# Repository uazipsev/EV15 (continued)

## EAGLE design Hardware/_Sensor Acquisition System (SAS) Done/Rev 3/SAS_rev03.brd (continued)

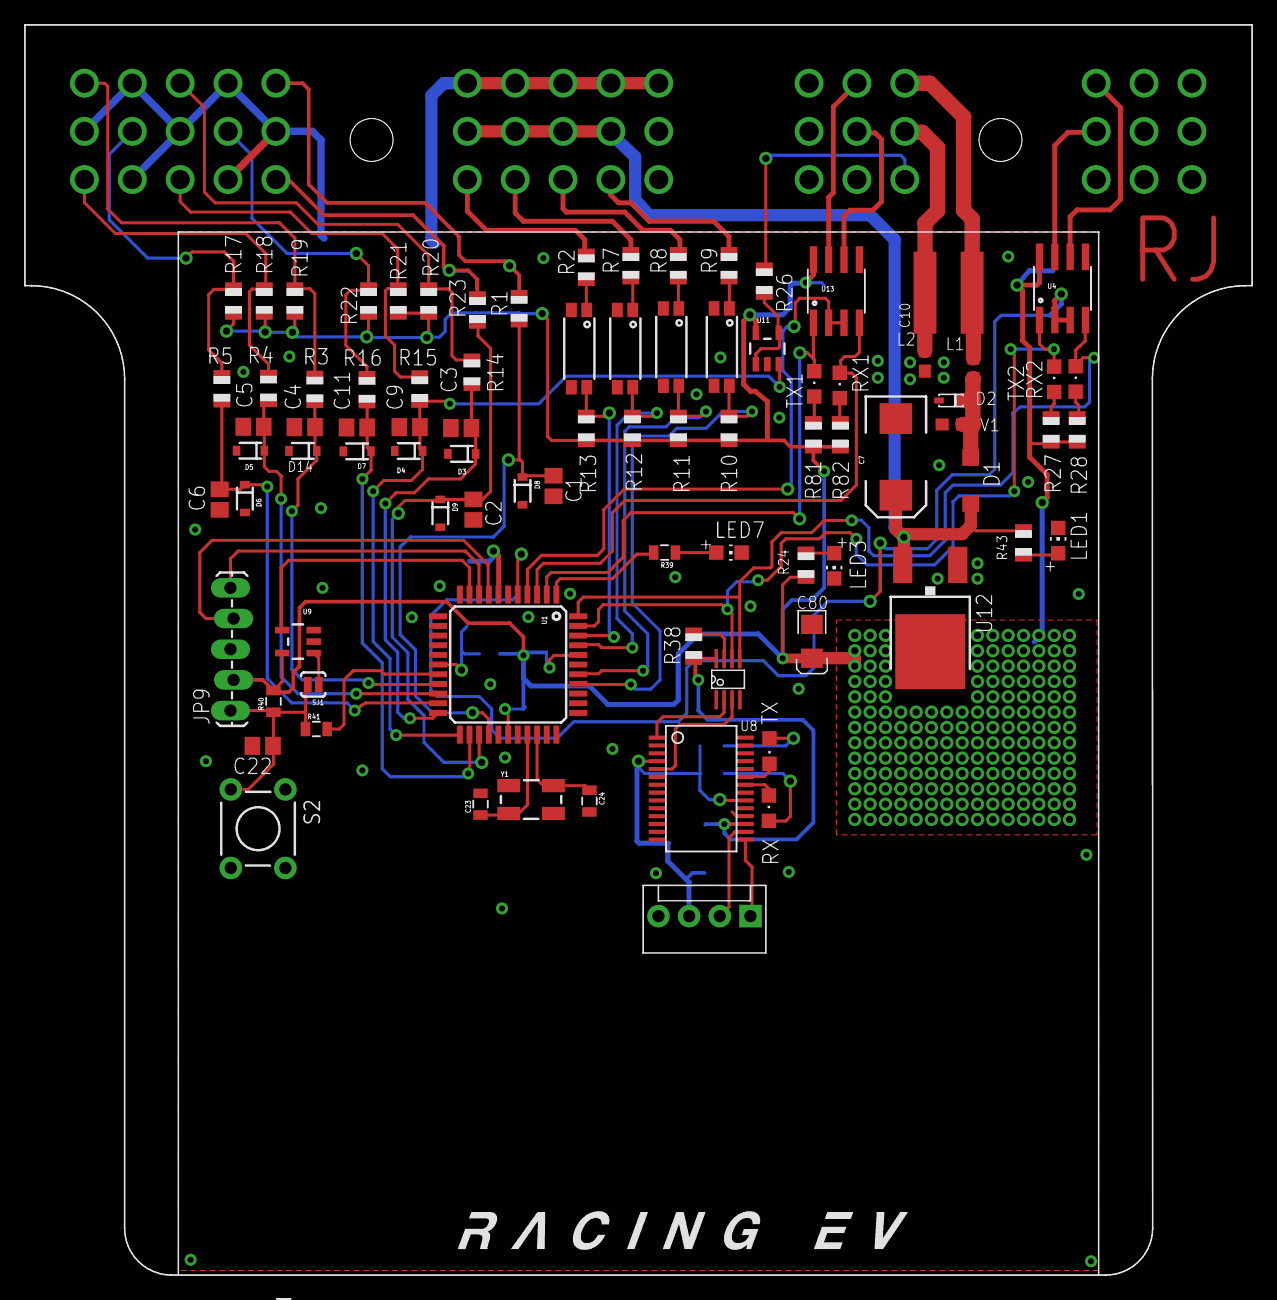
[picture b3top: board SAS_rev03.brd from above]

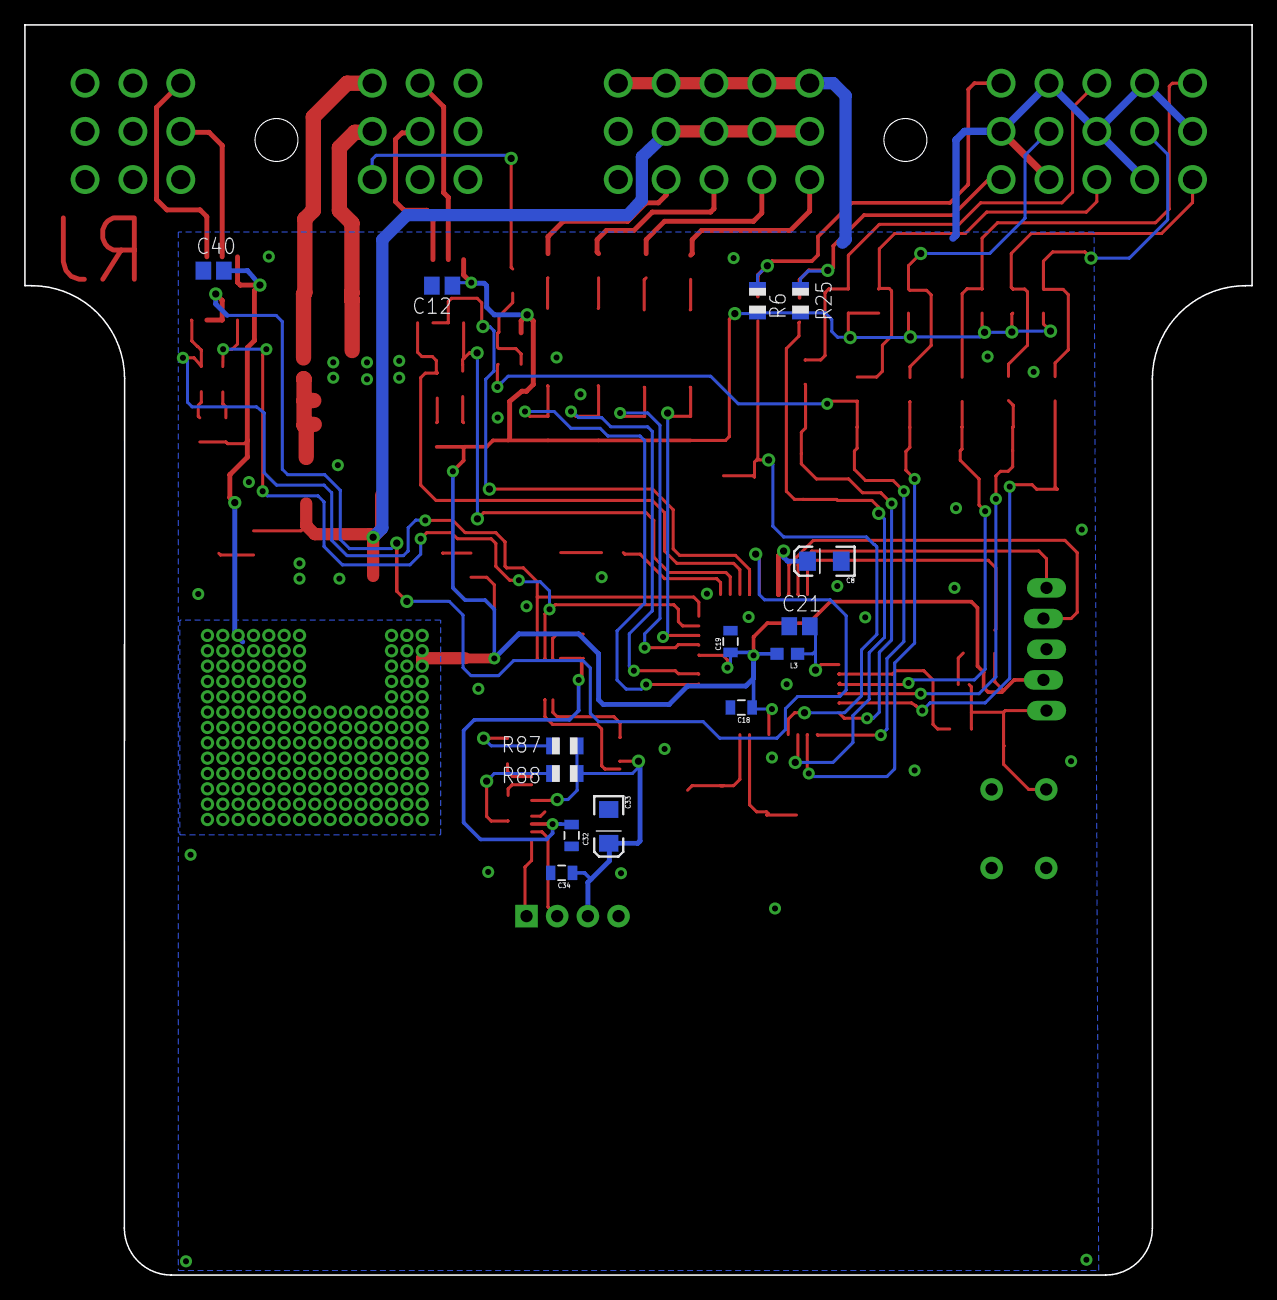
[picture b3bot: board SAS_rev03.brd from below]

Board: 2 copper layers, 101.6 x 103.5 mm, 102 parts (14 on the bottom side), 75 nets.

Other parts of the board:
U$2: L-L

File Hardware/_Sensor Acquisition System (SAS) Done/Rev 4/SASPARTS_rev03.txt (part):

Partlist

Exported from SAS_rev03.brd at 1/9/15 12:50 AM

EAGLE Version 6.5.0 Copyright (c) 1988-2013 CadSoft

Assembly variant: 

Part     Value             Package            Library                    Position (mil)        Orientation

C1       10uF              C0805              adafruit                   (-2282 2537)          R270
C2       10uF              C0805              adafruit                   (-2543 2460)          R270
C3       10uF              C0805              adafruit                   (-2583 2726)          R180
C4       10uF              C0805              adafruit                   (-3093 2729)          R180
C5       10uF              C0805              adafruit                   (-3260 2730)          R180
C6       10uF              C0805              adafruit                   (-3370 2493)          R270
C7       100uF             EIA7343            SparkFun-Capacitors        (-1166 2632)          R270
C8       10uF              EIA3216            SparkFun-Capacitors        (-2611 2292)          MR180
C9       10uF              C0805              adafruit                   (-2751 2729)          R180
C10      1000pF            C1825              adafruit                   (-994.19993 3167.25)  R180
C11      10uF              C0805              adafruit                   (-2923 2728)          R180
C12      .1uF              C0805              adafruit                   (-1365 3190)          MR180
C18      0.1uF             0805               SparkFun-Capacitors        (-2340 1815)          MR180
C19      0.1uF             0805               SparkFun-Capacitors        (-2305 2030)          MR90
C21      100n              C0805              adafruit                   (-2530 2080)          MR180
C22      10n               C0805              adafruit                   (-3230 1690)          R180
C23      12pF              0805               SparkFun-Capacitors        (-2520 1500)          R90
C24      12pF              0805               SparkFun-Capacitors        (-2165 1510)          R270
C32      0.1uf             0805               SparkFun                   (-1787 1398)          MR270
C33      10uF              EIA3216            SparkFun                   (-1908 1427.5)        MR270
C34      0.1uf             0805               SparkFun                   (-1754.5 1276)        MR180
C40      .1uF              C0805              adafruit                   (-620 3239)           MR180
C80      10uF              POLC1206           RJ's_parts                 (-1439.69993 2030.79995) R90
CASE2    581-01-48-009     581-01-48-009      FSAE Eletric               (-2005 3665)          R0
D1       1N4001            SOD123             diode                      (-921.89998 2555.20005) R90
D2       MM5Z30            SOD-523F           EmEndev                    (-986.10002 2815.79995) R0
D3       BZX384-B3V3       SOD-323            SparkFun                   (-2581 2642)          R180
D4       BZX384-B3V3       SOD-323            SparkFun                   (-2754 2651)          R180
D5       BZX384-B3V3       SOD-323            SparkFun                   (-3270 2652)          R180
D6       BZX384-B3V3       SOD-323            SparkFun                   (-3288 2496)          R270
D7       BZX384-B3V3       SOD-323            SparkFun                   (-2922 2650)          R180
D8       BZX384-B3V3       SOD-323            SparkFun                   (-2383 2521)          R270
D9       BZX384-B3V3       SOD-323            SparkFun                   (-2651 2448)          R270
D14      BZX384-B3V3       SOD-323            SparkFun                   (-3099 2651.5)        R180
JP1                        MOLEX-1X4          SparkFun-Connectors        (-1640 1135)          R180
JP9      ICSP              1X05_LOCK_LONGPADS SparkFun-Connectors        (-3335 1805)          R90
L1       FB                0603               EmEndev                    (-913.0999 2920.89998) R270
L2       FB                0603               EmEndev                    (-1071.70005 2944.94993) R270
L3       FB                0603               SparkFun-Passives          (-2490 1990)          MR180
LED1                       CHIP-LED0805       adafruit                   (-637 2359)           R0
LED3                       CHIP-LED0805       adafruit                   (-1367 2277)          R180
LED7                       CHIP-LED0805       adafruit                   (-1710 2320)          R270
R1       1k                R0805              adafruit                   (-2394 3115)          R90
R2       220               R0805              adafruit                   (-2175 3250)          R90
R3       1k                R0805              adafruit                   (-3060 2852)          R90
R4       1k                R0805              adafruit                   (-3211 2855)          R90
R5       1k                R0805              adafruit                   (-3363 2854)          R90
R6       10k               R0805              adafruit                   (-2393 3141)          MR270
R7       220               R0805              adafruit                   (-2030 3255)          R90
R8       220               R0805              adafruit                   (-1875 3255)          R90
R9       220               R0805              adafruit                   (-1710 3255)          R90
R10      10k               R0805              adafruit                   (-1710 2725)          R270
R11      10k               R0805              adafruit                   (-1875 2725)          R270
R12      10k               R0805              adafruit                   (-2025 2725)          R270
R13      10k               R0805              adafruit                   (-2175 2725)          R270
R14      1k                R0805              adafruit                   (-2548 2908)          R90
R15      1k                R0805              adafruit                   (-2718 2853)          R90
R16      1k                R0805              adafruit                   (-2890 2851)          R90
R17      10k               R0805              adafruit                   (-3325 3140)          R270
R18      10k               R0805              adafruit                   (-3225 3140)          R270
R19      10k               R0805              adafruit                   (-3125 3140)          R270
R20      10k               R0805              adafruit                   (-2689 3140)          R270
R21      10k               R0805              adafruit                   (-2788 3140)          R270
R22      10k               R0805              adafruit                   (-2885 3140)          R270
R23      1k                R0805              adafruit                   (-2530 3111)          R90
R24      499               R0805              adafruit                   (-1459 2279)          R270
R25      10k               R0805              adafruit                   (-2533 3141)          MR270
R26      10k               R0805              adafruit                   (-1595 3205)          R270
R27      1K                R0805              adafruit                   (-660 2720)           R270
R28      1k                R0805              adafruit                   (-575 2720)           R270
R38      1k                R0805              adafruit                   (-1825 2015)          R270
R39      499               0805               SparkFun-Passives          (-1920 2320)          R180
R40      10k               0805               SparkFun-Passives          (-3195 1835)          R90
R41      499               0805               SparkFun-Resistors         (-3055 1745)          R0
R43      1.2k              R0805              adafruit                   (-750.19993 2351.5999) R90
R81      1K                R0805              adafruit                   (-1435 2704)          R270
R82      1k                R0805              adafruit                   (-1347 2704)          R270
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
